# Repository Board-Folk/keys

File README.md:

# Retro Keyboard and Keyboard Adapter Repository

This is repository for retro keyboards and adapters that have been used for projects over the past few years originally intended for private use helping with other projects.

As people have been asking it was thought it'd be worthwhile putting them somewhere in case they're of use to anyone else. Many have just been prototypes and not many have been finished, 
but I'll add them as I go. 'More Fun Making It' Lee showed the finished Acorn Electron PS/2 interface in one of his videos about Mogwaay's Electron ULA replacement work, so I'm starting there.

In complement to the Electron interface, the BBC B/B+ PS/2 and USB and BBC Master PS/2 adapters have been completed, they plug on the keyboard headers too, they need finishing up a bit. BBC B ones now uploaded.

There are many more to add after that too. May add replica keyboard / Cherry MX boards to here also.

Please feel free to make these yourself. Most project folders contain at least their gerbers and code. There's no guarantee anything works. Try help, improve and share if you can.

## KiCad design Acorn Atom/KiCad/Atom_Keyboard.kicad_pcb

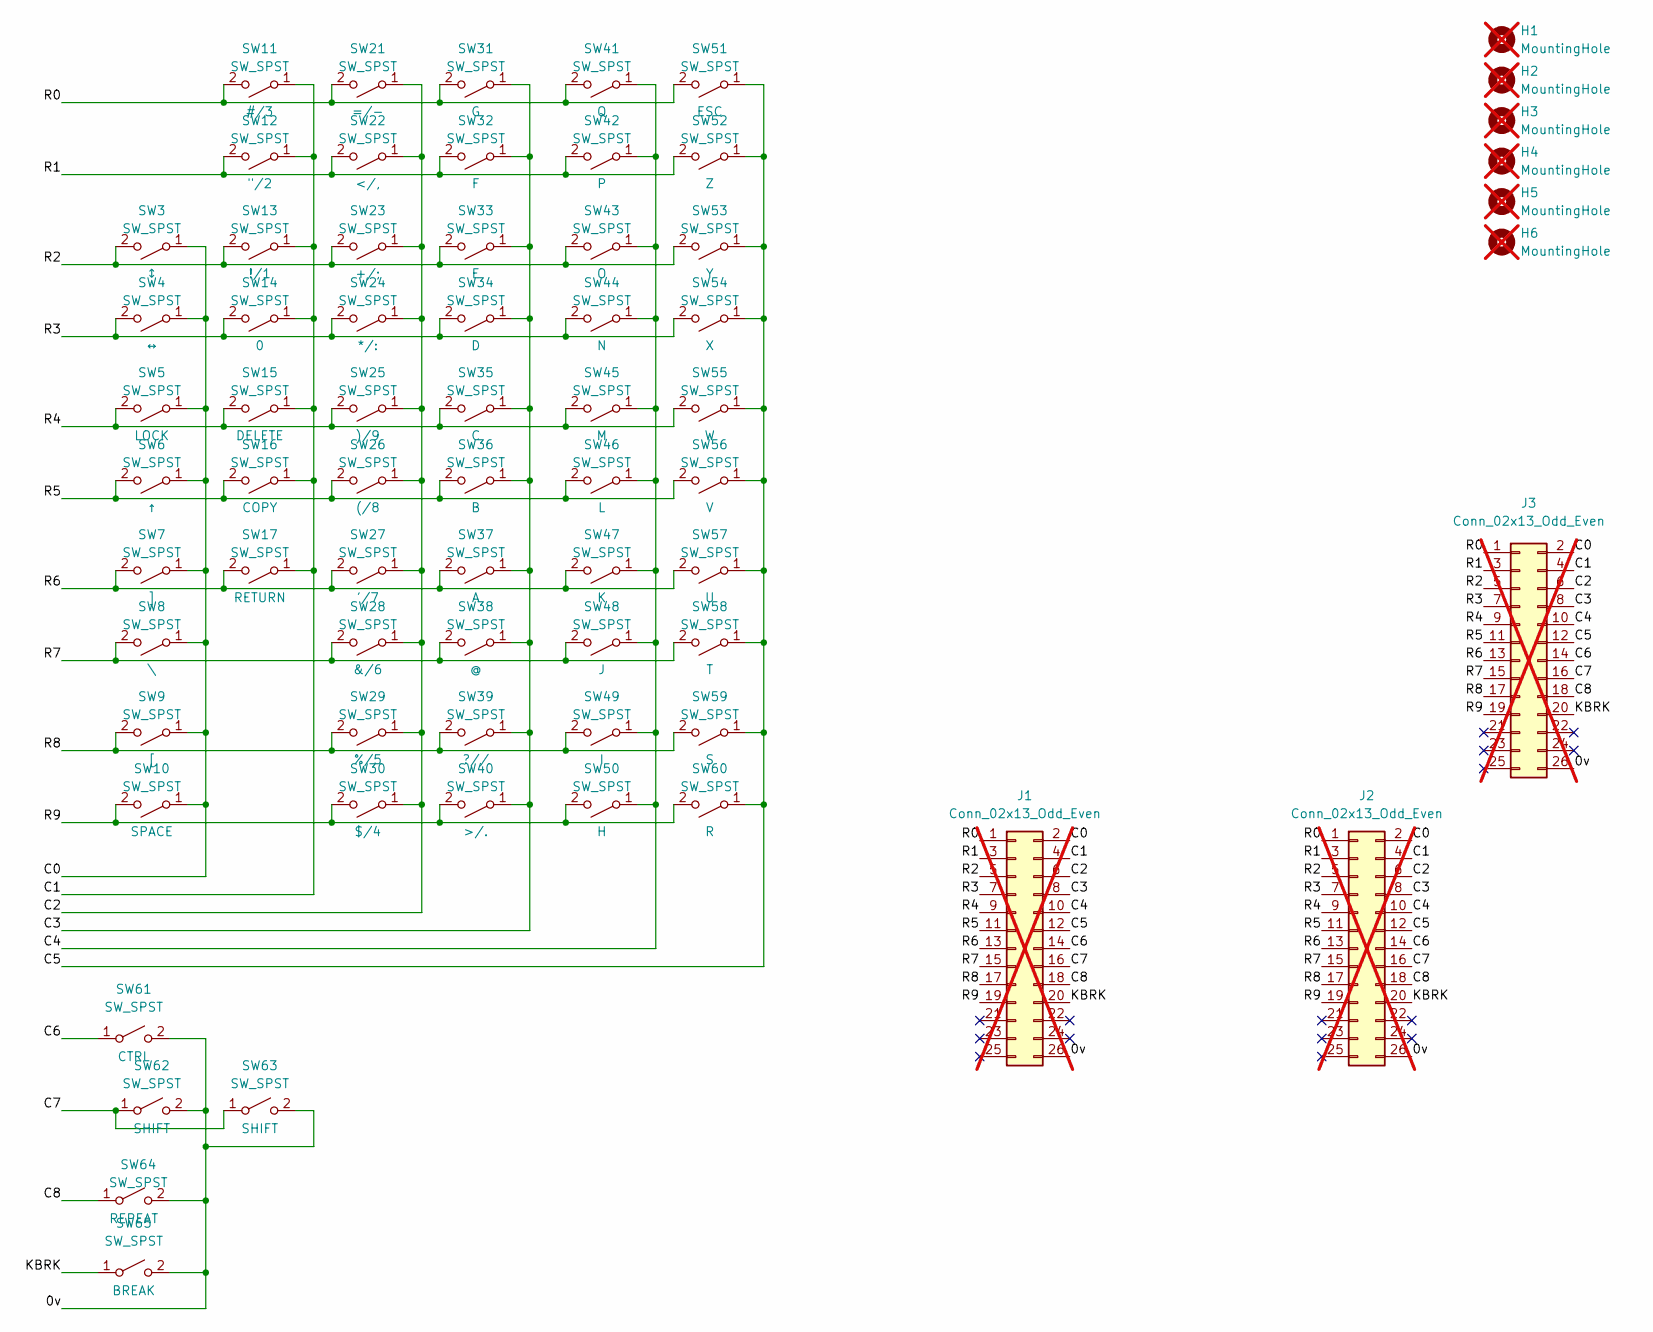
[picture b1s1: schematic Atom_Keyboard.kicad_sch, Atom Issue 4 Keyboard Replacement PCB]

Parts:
H1, H2, H3, H4, H5, H6: MountingHole; MountingHole_2.7mm_M2.5_DIN965; not fitted
J1, J2, J3: Conn_02x13_Odd_Even; IDC-Header_2x13_P2.54mm_Vertical; not fitted
SW3, SW4, SW5, SW6, SW7, SW8, SW9, SW11, SW12, SW13, SW14, SW15, SW16, SW17, SW21, SW22, SW23, SW24, SW25, SW26, SW27, SW28, SW29, SW30, SW31, SW32, SW33, SW34, SW35, SW36, SW37, SW38, SW39, SW40, SW41, SW42, SW43, SW44, SW45, SW46, SW47, SW48, SW49, SW50, SW51, SW52, SW53, SW54, SW55, SW56, SW57, SW58, SW59, SW60, SW61, SW62, SW63, SW64, SW65: SW_SPST; SW_Cherry_MX_1.00u_PCB
SW10: SW_SPST; SW_Cherry_MX_6.25u_PCB

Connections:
/0v: J1.26, J2.26, J3.26, SW61.2 (B), SW62.2 (B), SW63.2 (B), SW64.2 (B), SW65.2 (B)
/C0: J1.2, J2.2, J3.2, SW3.1 (A), SW4.1 (A), SW5.1 (A), SW6.1 (A), SW7.1 (A), SW8.1 (A), SW9.1 (A), SW10.1 (A)
/C1: J1.4, J2.4, J3.4, SW11.1 (A), SW12.1 (A), SW13.1 (A), SW14.1 (A), SW15.1 (A), SW16.1 (A), SW17.1 (A)
/C2: J1.6, J2.6, J3.6, SW21.1 (A), SW22.1 (A), SW23.1 (A), SW24.1 (A), SW25.1 (A), SW26.1 (A), SW27.1 (A), SW28.1 (A), SW29.1 (A), SW30.1 (A)
/C3: J1.8, J2.8, J3.8, SW31.1 (A), SW32.1 (A), SW33.1 (A), SW34.1 (A), SW35.1 (A), SW36.1 (A), SW37.1 (A), SW38.1 (A), SW39.1 (A), SW40.1 (A)
/C4: J1.10, J2.10, J3.10, SW41.1 (A), SW42.1 (A), SW43.1 (A), SW44.1 (A), SW45.1 (A), SW46.1 (A), SW47.1 (A), SW48.1 (A), SW49.1 (A), SW50.1 (A)
/C5: J1.12, J2.12, J3.12, SW51.1 (A), SW52.1 (A), SW53.1 (A), SW54.1 (A), SW55.1 (A), SW56.1 (A), SW57.1 (A), SW58.1 (A), SW59.1 (A), SW60.1 (A)
/C6: J1.14, J2.14, J3.14, SW61.1 (A)
/C7: J1.16, J2.16, J3.16, SW62.1 (A), SW63.1 (A)
/C8: J1.18, J2.18, J3.18, SW64.1 (A)
/KBRK: J1.20, J2.20, J3.20, SW65.1 (A)
/R0: J1.1, J2.1, J3.1, SW11.2 (B), SW21.2 (B), SW31.2 (B), SW41.2 (B), SW51.2 (B)
/R1: J1.3, J2.3, J3.3, SW12.2 (B), SW22.2 (B), SW32.2 (B), SW42.2 (B), SW52.2 (B)
/R2: J1.5, J2.5, J3.5, SW3.2 (B), SW13.2 (B), SW23.2 (B), SW33.2 (B), SW43.2 (B), SW53.2 (B)
/R3: J1.7, J2.7, J3.7, SW4.2 (B), SW14.2 (B), SW24.2 (B), SW34.2 (B), SW44.2 (B), SW54.2 (B)
/R4: J1.9, J2.9, J3.9, SW5.2 (B), SW15.2 (B), SW25.2 (B), SW35.2 (B), SW45.2 (B), SW55.2 (B)
/R5: J1.11, J2.11, J3.11, SW6.2 (B), SW16.2 (B), SW26.2 (B), SW36.2 (B), SW46.2 (B), SW56.2 (B)
/R6: J1.13, J2.13, J3.13, SW7.2 (B), SW17.2 (B), SW27.2 (B), SW37.2 (B), SW47.2 (B), SW57.2 (B)
/R7: J1.15, J2.15, J3.15, SW8.2 (B), SW28.2 (B), SW38.2 (B), SW48.2 (B), SW58.2 (B)
/R8: J1.17, J2.17, J3.17, SW9.2 (B), SW29.2 (B), SW39.2 (B), SW49.2 (B), SW59.2 (B)
/R9: J1.19, J2.19, J3.19, SW10.2 (B), SW30.2 (B), SW40.2 (B), SW50.2 (B), SW60.2 (B)

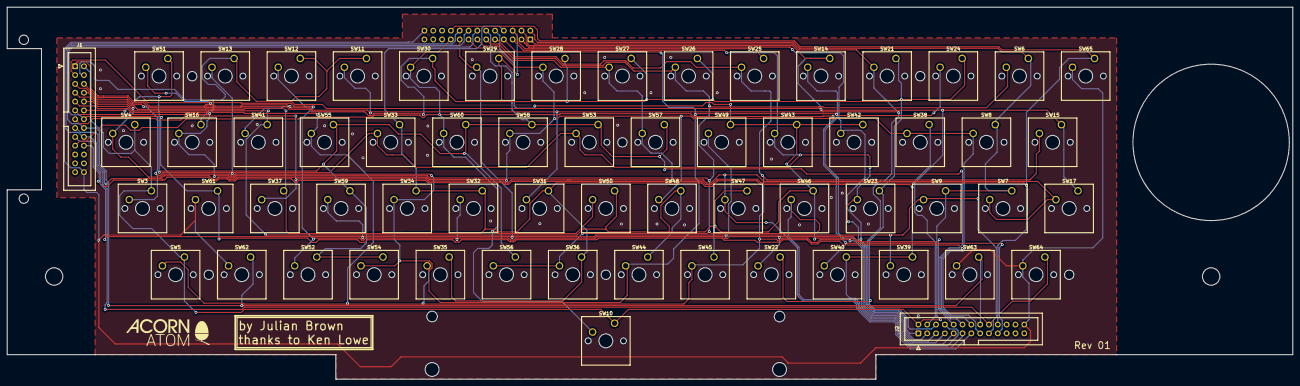
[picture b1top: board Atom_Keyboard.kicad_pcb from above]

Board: 2 copper layers, 370.0 x 107.1 mm, 69 parts (1 on the bottom side), 21 nets.

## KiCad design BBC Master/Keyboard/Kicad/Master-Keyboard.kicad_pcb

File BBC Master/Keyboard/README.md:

# BBC Master 128K (Full Size) Replica Keyboard

A replica keyboard for the full size BBC Master (not Compact). We believe this has been build successfully. Most of the tracks are on the back, former wire links now on the front as tracks.

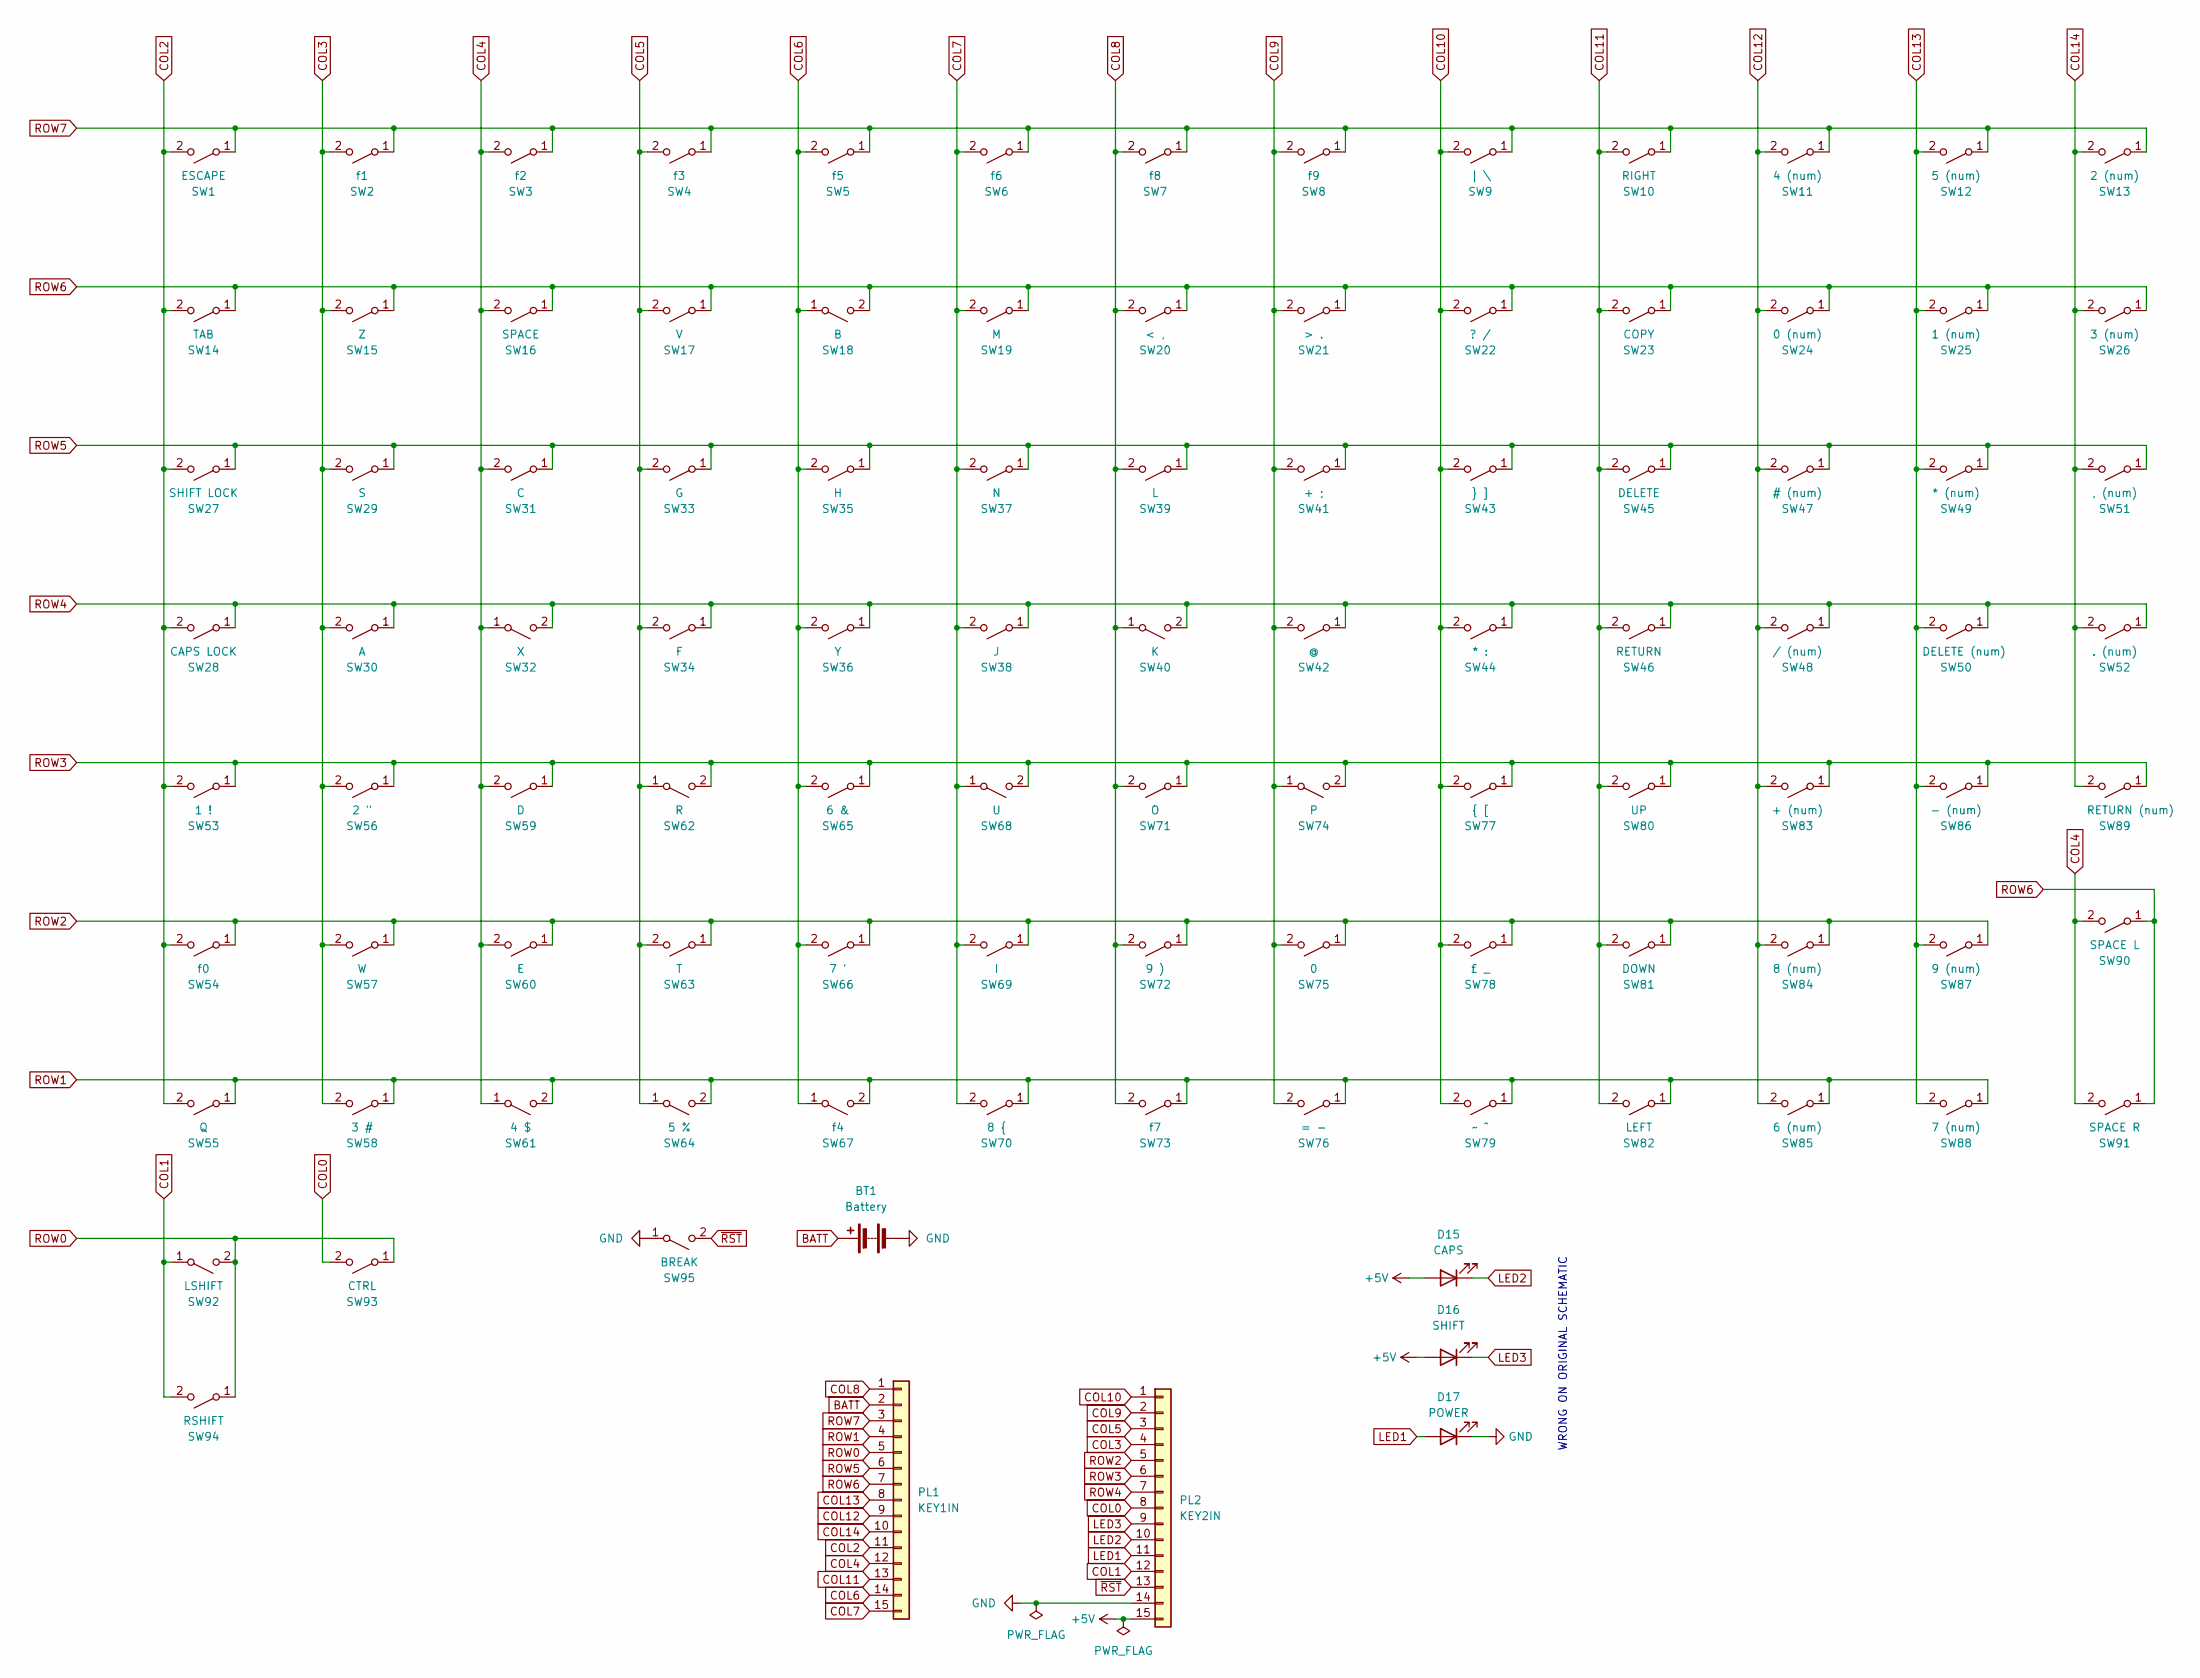
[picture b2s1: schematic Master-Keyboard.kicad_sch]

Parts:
BT1: Battery
D15: CAPS; LED_D2.54mm
D16: SHIFT; LED_D2.54mm
D17: POWER; LED_D2.54mm
PL1: KEY1IN; Header_1x15_P2.54mm
PL2: KEY2IN; Header_1x15_P2.54mm
SW1: ESCAPE; BBC Master KeySwitch
SW2: f1; BBC Master KeySwitch
SW3: f2; BBC Master KeySwitch
SW4: f3; BBC Master KeySwitch
SW5: f5; BBC Master KeySwitch
SW6: f6; BBC Master KeySwitch
SW7: f8; BBC Master KeySwitch
SW8: f9; BBC Master KeySwitch
SW9: | \; BBC Master KeySwitch
SW10: RIGHT; BBC Master KeySwitch
SW11: 4 (num); BBC Master KeySwitch
SW12: 5 (num); BBC Master KeySwitch
SW13: 2 (num); BBC Master KeySwitch
SW14: TAB; BBC Master KeySwitch
SW15: Z; BBC Master KeySwitch
SW16: SPACE; BBC Master KeySwitch
SW17: V; BBC Master KeySwitch
SW18: B; BBC Master KeySwitch
SW19: M; BBC Master KeySwitch
SW20: < ,; BBC Master KeySwitch
SW21: > .; BBC Master KeySwitch
SW22: ? /; BBC Master KeySwitch
SW23: COPY; BBC Master KeySwitch
SW24: 0 (num); BBC Master KeySwitch
SW25: 1 (num); BBC Master KeySwitch
SW26: 3 (num); BBC Master KeySwitch
SW27: SHIFT LOCK; BBC Master KeySwitch
SW28: CAPS LOCK; BBC Master KeySwitch
SW29: S; BBC Master KeySwitch
SW30: A; BBC Master KeySwitch
SW31: C; BBC Master KeySwitch
SW32: X; BBC Master KeySwitch
SW33: G; BBC Master KeySwitch
SW34: F; BBC Master KeySwitch
SW35: H; BBC Master KeySwitch
SW36: Y; BBC Master KeySwitch
SW37: N; BBC Master KeySwitch
SW38: J; BBC Master KeySwitch
SW39: L; BBC Master KeySwitch
SW40: K; BBC Master KeySwitch
SW41: + ;; BBC Master KeySwitch
SW42: @; BBC Master KeySwitch
SW43: } ]; BBC Master KeySwitch
SW44: * :; BBC Master KeySwitch
SW45: DELETE; BBC Master KeySwitch
SW46: RETURN; BBC Master KeySwitch
SW47: # (num); BBC Master KeySwitch
SW48: / (num); BBC Master KeySwitch
SW49: * (num); BBC Master KeySwitch
SW50: DELETE (num); BBC Master KeySwitch
SW51: , (num); BBC Master KeySwitch
SW52: . (num); BBC Master KeySwitch
SW53: 1 !; BBC Master KeySwitch
SW54: f0; BBC Master KeySwitch
SW55: Q; BBC Master KeySwitch
SW56: 2 "; BBC Master KeySwitch
SW57: W; BBC Master KeySwitch
SW58: 3 #; BBC Master KeySwitch
SW59: D; BBC Master KeySwitch
SW60: E; BBC Master KeySwitch
SW61: 4 $; BBC Master KeySwitch
SW62: R; BBC Master KeySwitch
SW63: T; BBC Master KeySwitch
SW64: 5 %; BBC Master KeySwitch
SW65: 6 &; BBC Master KeySwitch
SW66: 7 '; BBC Master KeySwitch
SW67: f4; BBC Master KeySwitch
SW68: U; BBC Master KeySwitch
SW69: I; BBC Master KeySwitch
SW70: 8 {; BBC Master KeySwitch
SW71: O; BBC Master KeySwitch
SW72: 9 ); BBC Master KeySwitch
SW73: f7; BBC Master KeySwitch
SW74: P; BBC Master KeySwitch
SW75: 0; BBC Master KeySwitch
SW76: = -; BBC Master KeySwitch
SW77: { [; BBC Master KeySwitch
SW78: £ _; BBC Master KeySwitch
SW79: ~ ^; BBC Master KeySwitch
SW80: UP; BBC Master KeySwitch
SW81: DOWN; BBC Master KeySwitch
SW82: LEFT; BBC Master KeySwitch
SW83: + (num); BBC Master KeySwitch
SW84: 8 (num); BBC Master KeySwitch
SW85: 6 (num); BBC Master KeySwitch
SW86: - (num); BBC Master KeySwitch
SW87: 9 (num); BBC Master KeySwitch
SW88: 7 (num); BBC Master KeySwitch
SW89: RETURN (num); BBC Master KeySwitch
SW90: SPACE L; BBC Master KeySwitch
SW91: SPACE R; BBC Master KeySwitch
SW92: LSHIFT; BBC Master KeySwitch
SW93: CTRL; BBC Master KeySwitch
SW94: RSHIFT; BBC Master KeySwitch
SW95: BREAK; BBC Master KeySwitch

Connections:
+5V: D15.2 (A), D16.2 (A), PL2.15
BATT: BT1.1 (+), PL1.2
COL0: PL2.8, SW93.2 (B)
COL1: PL2.12, SW92.1 (A), SW94.2 (B)
COL2: PL1.11, SW1.2 (B), SW14.2 (B), SW27.2 (B), SW28.2 (B), SW53.2 (B), SW54.2 (B), SW55.2 (B)
COL3: PL2.4, SW2.2 (B), SW15.2 (B), SW29.2 (B), SW30.2 (B), SW56.2 (B), SW57.2 (B), SW58.2 (B)
COL4: PL1.12, SW3.2 (B), SW16.2 (B), SW31.2 (B), SW32.1 (A), SW59.2 (B), SW60.2 (B), SW61.1 (A), SW90.2 (B), SW91.2 (B)
COL5: PL2.3, SW4.2 (B), SW17.2 (B), SW33.2 (B), SW34.2 (B), SW62.1 (A), SW63.2 (B), SW64.1 (A)
COL6: PL1.14, SW5.2 (B), SW18.1 (A), SW35.2 (B), SW36.2 (B), SW65.2 (B), SW66.2 (B), SW67.1 (A)
COL7: PL1.15, SW6.2 (B), SW19.2 (B), SW37.2 (B), SW38.2 (B), SW68.1 (A), SW69.2 (B), SW70.2 (B)
COL8: PL1.1, SW7.2 (B), SW20.2 (B), SW39.2 (B), SW40.1 (A), SW71.2 (B), SW72.2 (B), SW73.2 (B)
COL9: PL2.2, SW8.2 (B), SW21.2 (B), SW41.2 (B), SW42.2 (B), SW74.1 (A), SW75.2 (B), SW76.2 (B)
COL10: PL2.1, SW9.2 (B), SW22.2 (B), SW43.2 (B), SW44.2 (B), SW77.2 (B), SW78.2 (B), SW79.2 (B)
COL11: PL1.13, SW10.2 (B), SW23.2 (B), SW45.2 (B), SW46.2 (B), SW80.2 (B), SW81.2 (B), SW82.2 (B)
COL12: PL1.9, SW11.2 (B), SW24.2 (B), SW47.2 (B), SW48.2 (B), SW83.2 (B), SW84.2 (B), SW85.2 (B)
COL13: PL1.8, SW12.2 (B), SW25.2 (B), SW49.2 (B), SW50.2 (B), SW86.2 (B), SW87.2 (B), SW88.2 (B)
COL14: PL1.10, SW13.2 (B), SW26.2 (B), SW51.2 (B), SW52.2 (B), SW89.2 (B)
GND: BT1.2 (-), D17.1 (K), PL2.14, SW95.1 (A)
LED1: D17.2 (A), PL2.11
LED2: D15.1 (K), PL2.10
LED3: D16.1 (K), PL2.9
ROW0: PL1.5, SW92.2 (B), SW93.1 (A), SW94.1 (A)
ROW1: PL1.4, SW55.1 (A), SW58.1 (A), SW61.2 (B), SW64.2 (B), SW67.2 (B), SW70.1 (A), SW73.1 (A), SW76.1 (A), SW79.1 (A), SW82.1 (A), SW85.1 (A), SW88.1 (A)
ROW2: PL2.5, SW54.1 (A), SW57.1 (A), SW60.1 (A), SW63.1 (A), SW66.1 (A), SW69.1 (A), SW72.1 (A), SW75.1 (A), SW78.1 (A), SW81.1 (A), SW84.1 (A), SW87.1 (A)
ROW3: PL2.6, SW53.1 (A), SW56.1 (A), SW59.1 (A), SW62.2 (B), SW65.1 (A), SW68.2 (B), SW71.1 (A), SW74.2 (B), SW77.1 (A), SW80.1 (A), SW83.1 (A), SW86.1 (A), SW89.1 (A)
ROW4: PL2.7, SW28.1 (A), SW30.1 (A), SW32.2 (B), SW34.1 (A), SW36.1 (A), SW38.1 (A), SW40.2 (B), SW42.1 (A), SW44.1 (A), SW46.1 (A), SW48.1 (A), SW50.1 (A), SW52.1 (A)
ROW5: PL1.6, SW27.1 (A), SW29.1 (A), SW31.1 (A), SW33.1 (A), SW35.1 (A), SW37.1 (A), SW39.1 (A), SW41.1 (A), SW43.1 (A), SW45.1 (A), SW47.1 (A), SW49.1 (A), SW51.1 (A)
ROW6: PL1.7, SW14.1 (A), SW15.1 (A), SW16.1 (A), SW17.1 (A), SW18.2 (B), SW19.1 (A), SW20.1 (A), SW21.1 (A), SW22.1 (A), SW23.1 (A), SW24.1 (A), SW25.1 (A), SW26.1 (A), SW90.1 (A), SW91.1 (A)
ROW7: PL1.3, SW1.1 (A), SW2.1 (A), SW3.1 (A), SW4.1 (A), SW5.1 (A), SW6.1 (A), SW7.1 (A), SW8.1 (A), SW9.1 (A), SW10.1 (A), SW11.1 (A), SW12.1 (A), SW13.1 (A)
~RST: PL2.13, SW95.2 (B)

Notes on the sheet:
WRONG ON ORIGINAL SCHEMATIC

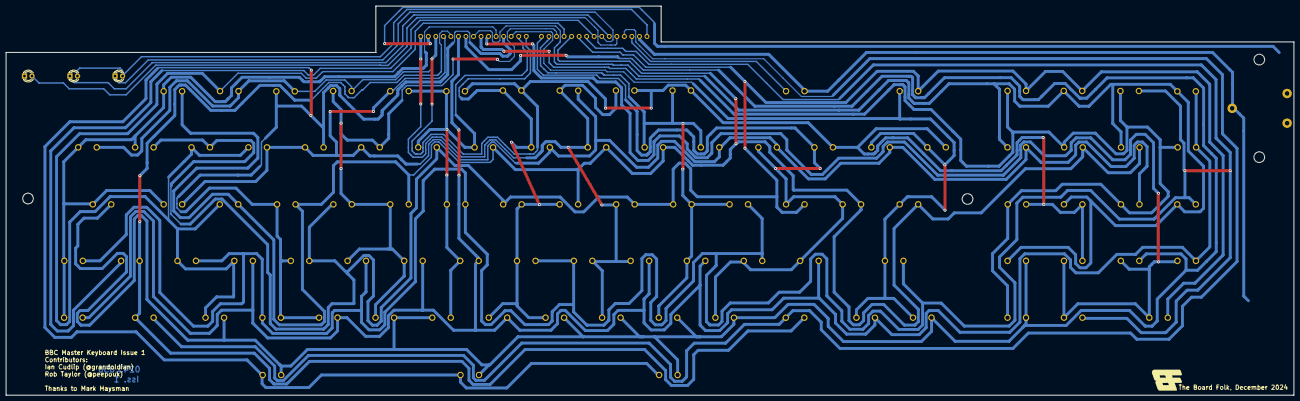
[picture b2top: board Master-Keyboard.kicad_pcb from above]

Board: 2 copper layers, 434.0 x 131.1 mm, 101 parts (0 on the bottom side), 30 nets.

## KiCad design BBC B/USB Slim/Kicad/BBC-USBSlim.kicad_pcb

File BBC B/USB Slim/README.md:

# BBC B/B+ USB Slim v1

This is a surface mount board designed to fit inside the BBC's case, though currently does not work with the original keyboard connected. Uses the Seeduino XIAO. The XIAO does take a few seconds to boot and recognise the keyboard, it's not as quick as the Atmega version.

* BOM

iBOM for the board.

* Gerber

Gerbers and gerber zip file for production.

* Kicad

Kicad project for the board.

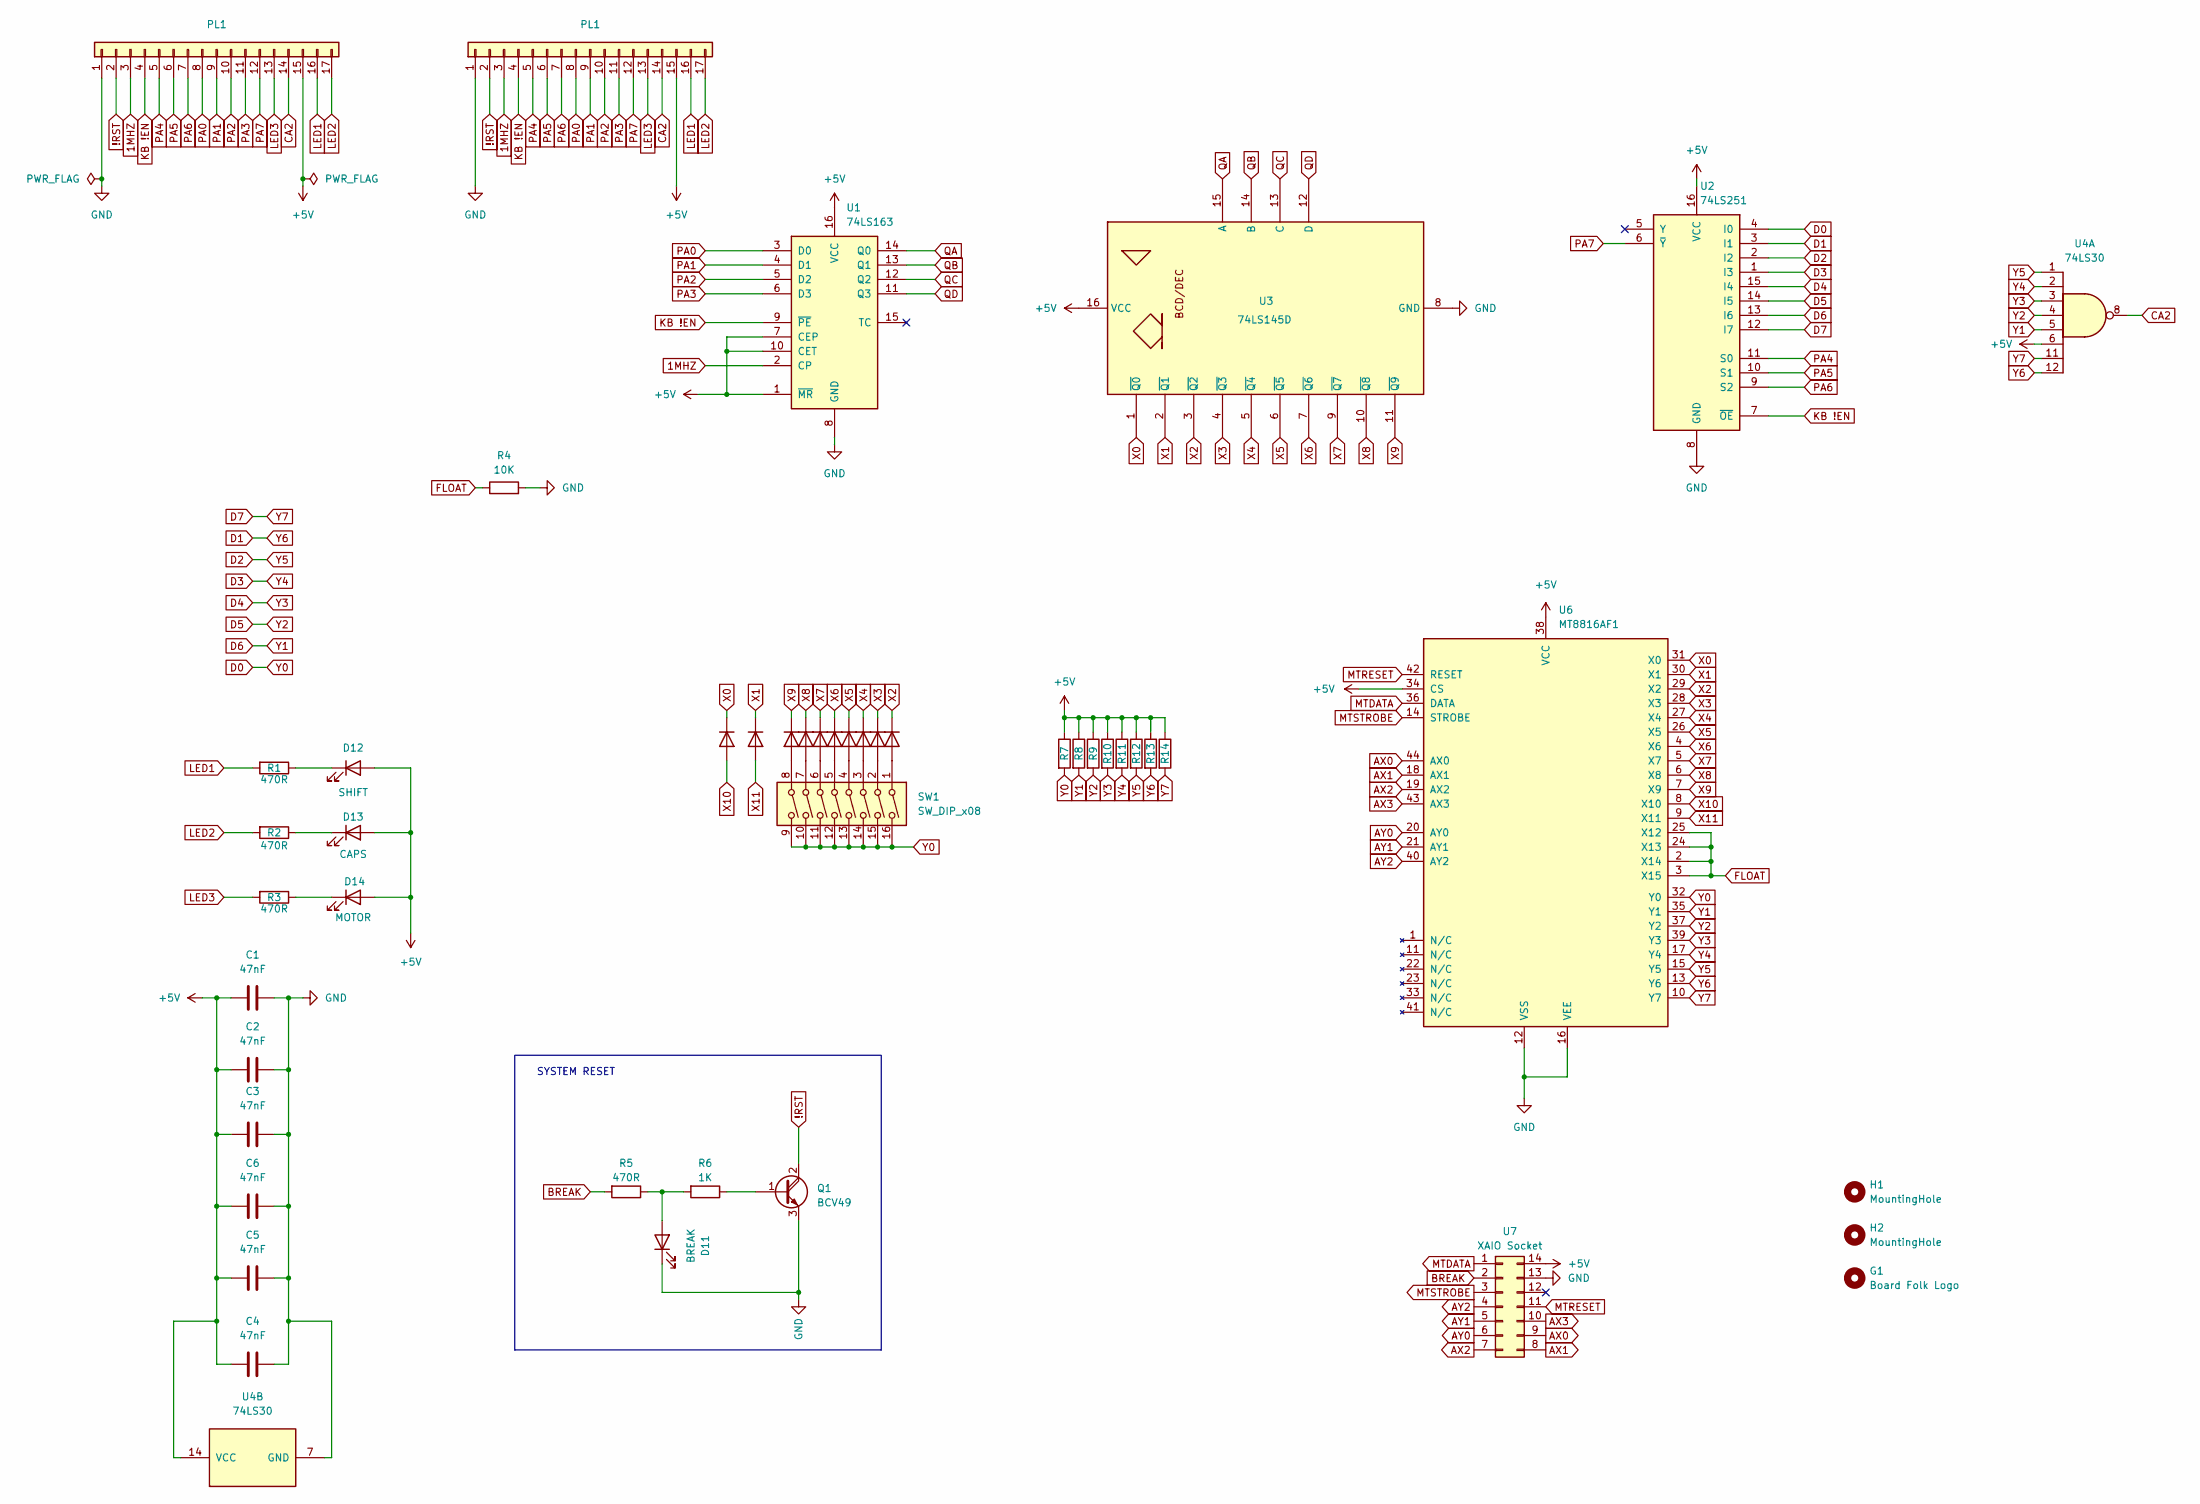
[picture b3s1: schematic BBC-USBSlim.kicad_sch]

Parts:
C1, C2, C3, C4, C5, C6: 47nF; C_0805_2012Metric
D1, D2, D3, D4, D5, D6, D7, D8, D9, D10: 1N4148; MINIDIODE
D11: BREAK; LED_1206_3216Metric
D12: SHIFT; LED_1206_3216Metric
D13: CAPS; LED_1206_3216Metric
D14: MOTOR; LED_1206_3216Metric
G1: Board Folk Logo; BF8
H1, H2: MountingHole; MountingHole_2.5mm
J1, J3: PL1; PinHeader_1x17_P2.54mm_Vertical
Q1: BCV49; SOT-89-3
R1, R2, R3, R5: 470R; R_0805_2012Metric
R4: 10K; R_0805_2012Metric
R6: 1K; R_0805_2012Metric
R7, R8, R9, R10, R11, R12, R13, R14: 2K2; R_0805_2012Metric
SW1: SW_DIP_x08; DIP-16_W7.62mm
U1: 74LS163; SOIC-16_3.9x9.9mm_P1.27mm
U2: 74LS251; SOIC-16_3.9x9.9mm_P1.27mm
U3: 74LS145D; SOIC-16_3.9x9.9mm_P1.27mm
U4: 74LS30; SOIC-14_3.9x8.7mm_P1.27mm
U6: MT8816AF1; TQFP-44_10x10mm_P0.8mm
U7: XAIO Socket; XAIO 14PIN

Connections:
1MHZ: J1.3, J3.3, U1.2 (CP)
!RST: J1.2, J3.2, Q1.2 (C)
+5V: C1.1, C2.1, C3.1, C4.1, C5.1, C6.1, D12.2 (A), D13.2 (A), D14.2 (A), J1.15, J3.15, R7.1, R8.1, R9.1, R10.1, R11.1, R12.1, R13.1, R14.1, U1.1 (~MR), U1.7 (CEP), U1.10 (CET), U1.16 (VCC), U2.16 (VCC), U3.16 (VCC), U4.6, U4.14 (VCC), U6.34 (CS), U6.38 (VCC), U7.14
AX0: U6.44 (AX0), U7.9
AX1: U6.18 (AX1), U7.8
AX2: U6.19 (AX2), U7.7
AX3: U6.43 (AX3), U7.10
AY0: U6.20 (AY0), U7.6
AY1: U6.21 (AY1), U7.5
AY2: U6.40 (AY2), U7.4
BREAK: R5.2, U7.2
CA2: J1.14, J3.14, U4.8
D0: R7.2, SW1.9, SW1.10, SW1.11, SW1.12, SW1.13, SW1.14, SW1.15, SW1.16, U2.4 (I0), U6.32 (Y0)
D1: R13.2, U2.3 (I1), U4.12, U6.13 (Y6)
D2: R12.2, U2.2 (I2), U4.1, U6.15 (Y5)
D3: R11.2, U2.1 (I3), U4.2, U6.17 (Y4)
D4: R10.2, U2.15 (I4), U4.3, U6.39 (Y3)
D5: R9.2, U2.14 (I5), U4.4, U6.37 (Y2)
D6: R8.2, U2.13 (I6), U4.5, U6.35 (Y1)
D7: R14.2, U2.12 (I7), U4.11, U6.10 (Y7)
FLOAT: R4.1, U6.2 (X14), U6.3 (X15), U6.24 (X13), U6.25 (X12)
GND: C1.2, C2.2, C3.2, C4.2, C5.2, C6.2, D11.1 (K), J1.1, J3.1, Q1.3 (E), R4.2, U1.8 (GND), U2.8 (GND), U3.8 (GND), U4.7 (GND), U6.12 (VSS), U6.16 (VEE), U7.13
KB !EN: J1.4, J3.4, U1.9 (~PE), U2.7 (~OE)
LED1: J1.16, J3.16, R1.2
LED2: J1.17, J3.17, R2.2
LED3: J1.13, J3.13, R3.2
MTDATA: U6.36 (DATA), U7.1
MTRESET: U6.42 (RESET), U7.11
MTSTROBE: U6.14 (STROBE), U7.3
unnamed: D3.2 (A), SW1.1
unnamed: D4.2 (A), SW1.2
unnamed: D5.2 (A), SW1.3
unnamed: D6.2 (A), SW1.4
unnamed: D7.2 (A), SW1.5
unnamed: D8.2 (A), SW1.6
unnamed: D9.2 (A), SW1.7
unnamed: D10.2 (A), SW1.8
unnamed: D11.2 (A), R5.1, R6.2
unnamed: D12.1 (K), R1.1
unnamed: D13.1 (K), R2.1
unnamed: D14.1 (K), R3.1
unnamed: Q1.1 (B), R6.1
PA0: J1.8, J3.8, U1.3 (D0)
PA1: J1.9, J3.9, U1.4 (D1)
PA2: J1.10, J3.10, U1.5 (D2)
PA3: J1.11, J3.11, U1.6 (D3)
PA4: J1.5, J3.5, U2.11 (S0)
PA5: J1.6, J3.6, U2.10 (S1)
PA6: J1.7, J3.7, U2.9 (S2)
PA7: J1.12, J3.12, U2.6 (~Y)
QA: U1.14 (Q0), U3.15 (A)
QB: U1.13 (Q1), U3.14 (B)
QC: U1.12 (Q2), U3.13 (C)
QD: U1.11 (Q3), U3.12 (D)
X0: D1.1 (K), U3.1 (~Q0), U6.31 (X0)
X1: D2.1 (K), U3.2 (~Q1), U6.30 (X1)
X2: D3.1 (K), U3.3 (~Q2), U6.29 (X2)
X3: D4.1 (K), U3.4 (~Q3), U6.28 (X3)
X4: D5.1 (K), U3.5 (~Q4), U6.27 (X4)
X5: D6.1 (K), U3.6 (~Q5), U6.26 (X5)
X6: D7.1 (K), U3.7 (~Q6), U6.4 (X6)
X7: D8.1 (K), U3.9 (~Q7), U6.5 (X7)
X8: D9.1 (K), U3.10 (~Q8), U6.6 (X8)
X9: D10.1 (K), U3.11 (~Q9), U6.7 (X9)
X10: D1.2 (A), U6.8 (X10)
X11: D2.2 (A), U6.9 (X11)

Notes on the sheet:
SYSTEM RESET

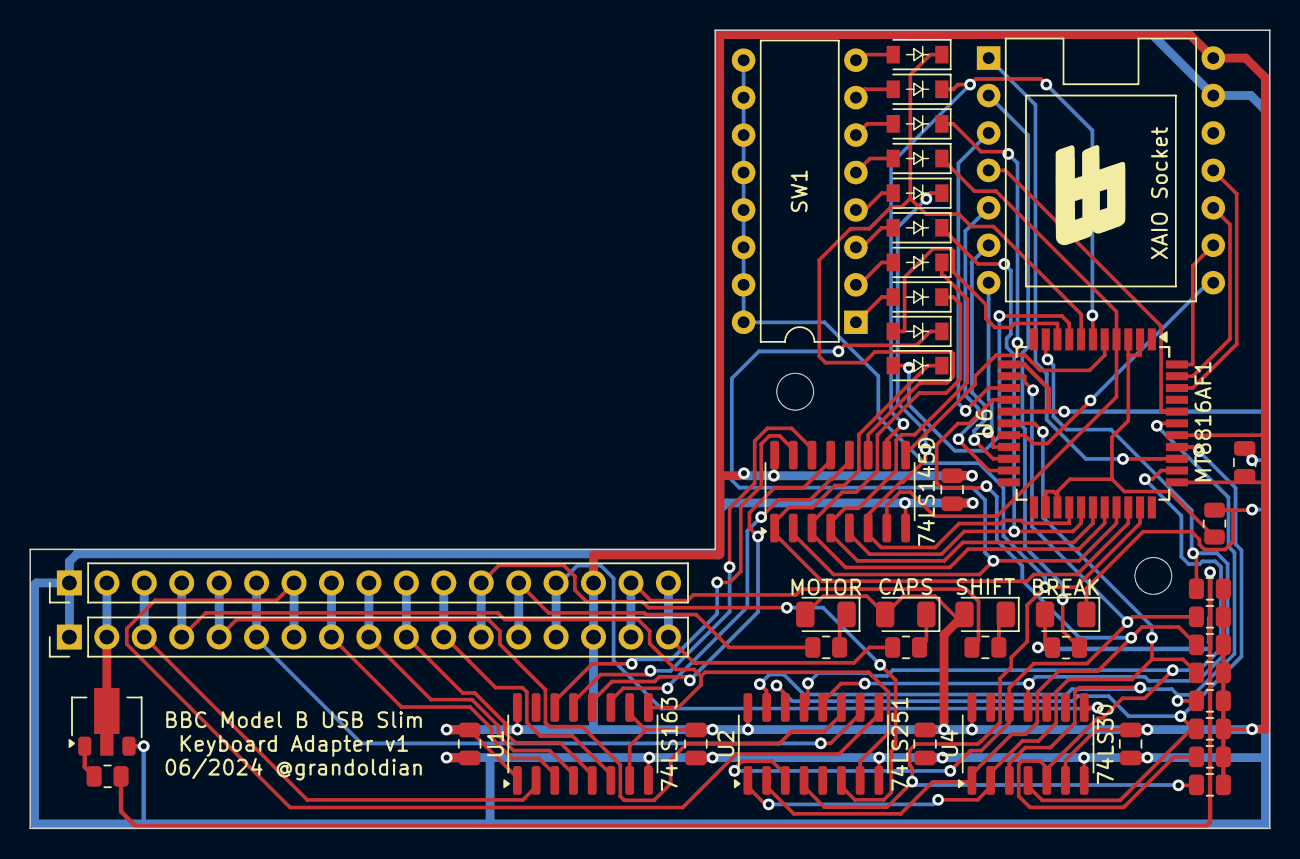
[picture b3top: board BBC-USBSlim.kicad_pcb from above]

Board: 2 copper layers, 84.1 x 54.1 mm, 47 parts (0 on the bottom side), 66 nets.

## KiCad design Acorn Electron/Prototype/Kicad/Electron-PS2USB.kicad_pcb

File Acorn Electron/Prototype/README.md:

# Acorn Electron Prototype Board v0

A PS/2 and potentially USB keyboard interface for the Acorn Electron based on C64keyboard by Robert VanHazinga using an Arduino type board and an MT8816 switch chip. This is the original throughhole board. 
It won't fit inside the case with the lid on, but is easy to build. The PS/2 configuration is for Arduino Nano, the USB, Seeeduino XIAO, same as the original project. USB code not done yet.
You may need to toggle Arduino IDE between processor ATmega328P and ATmega328P (old bootloader) depending on which Nano you have.

* BOM

iBOM for the board.

* Gerber

Gerbers and gerber zip file for production.

* Kicad

Kicad project for the board.

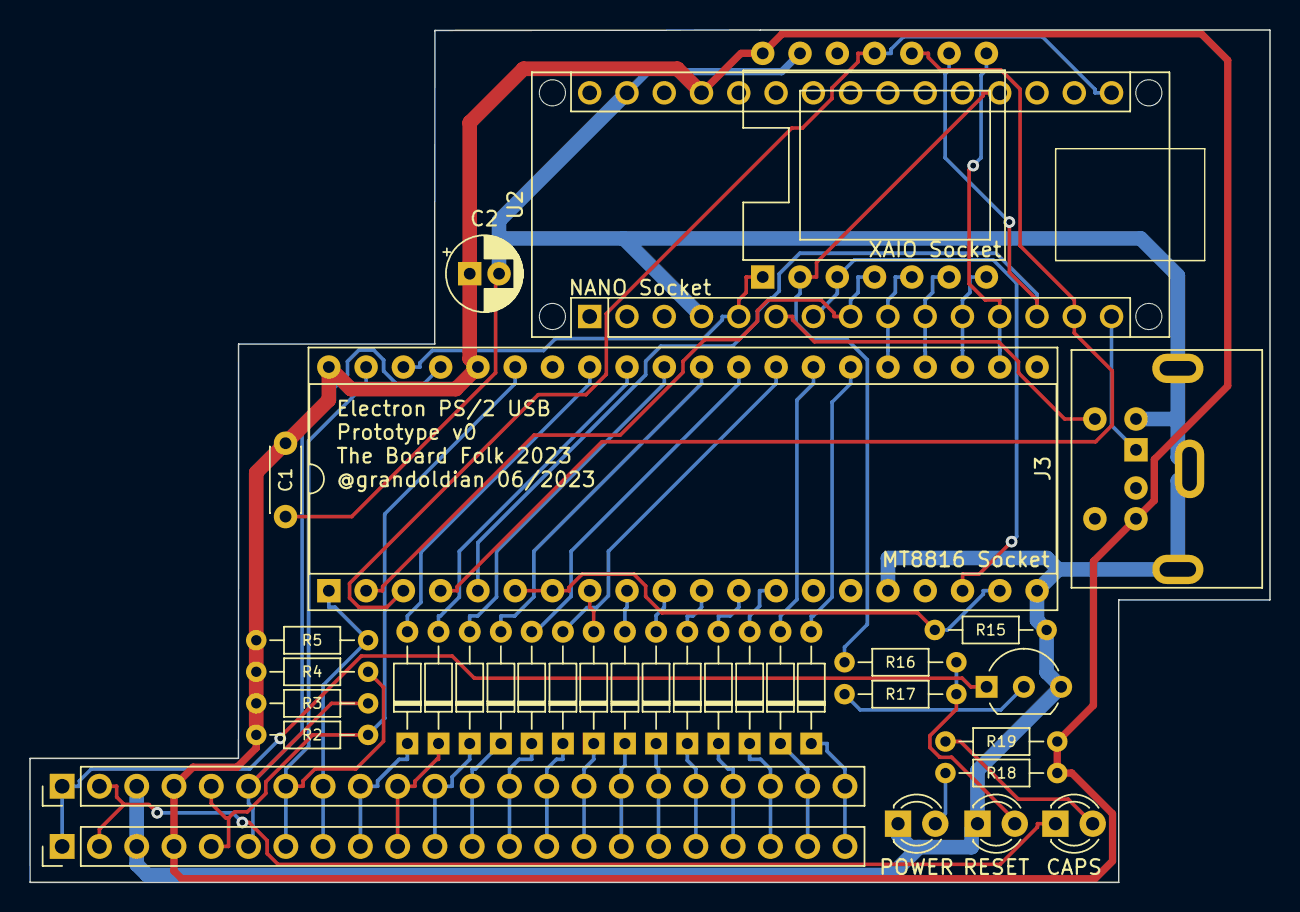
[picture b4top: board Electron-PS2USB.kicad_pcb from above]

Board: 2 copper layers, 84.5 x 58.1 mm, 35 parts (0 on the bottom side), 54 nets.

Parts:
C1: 47nF; C_Disc_D4.3mm_W1.9mm_P5.00mm
C2: 47uF; CP_Radial_D5.0mm_P2.00mm
CP1, CP2: KEYBOARD; PinHeader_1x22_P2.54mm_Vertical
D1, D2, D3, D4, D5, D6, D7, D8, D9, D10, D11, D12, D13, D14: D; D_DO-34_SOD68_P7.62mm_Horizontal
D15: POWER; LED_D3.0mm
D16: RESET; LED_D3.0mm
D17: CAPS; LED_D3.0mm
J3: PS/2; Connector_Mini-DIN_Female_6Pin_2rows
Q1: BC517; TO-92_Inline_Wide
R2, R3, R4, R5: R; R_Axial_DIN0204_L3.6mm_D1.6mm_P7.62mm_Horizontal
R15: 10K; R_Axial_DIN0204_L3.6mm_D1.6mm_P7.62mm_Horizontal
R16: 470R; R_Axial_DIN0204_L3.6mm_D1.6mm_P7.62mm_Horizontal
R17, R18, R19: 1K; R_Axial_DIN0204_L3.6mm_D1.6mm_P7.62mm_Horizontal
U1: MT8816 Socket; DIP-40_W15.24mm_Socket
U2: NANO Socket; Arduino_Nano_WithMountingHoles
U7: XAIO Socket; XAIO 14PIN

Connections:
!RST: CP1.1, CP2.1, Q1.1 (C)
+5V: C1.2, C2.1, CP1.4, CP2.4, J3.4, R2.2, R3.2, R4.2, R5.2, R18.1, R19.1, U1.36, U1.40, U2.27, U7.14
/A0: CP1.18, CP2.18, D10.1 (K)
/A1: CP1.19, CP2.19, D11.1 (K)
/A2: CP1.20, CP2.20, D12.1 (K)
/A3: CP1.21, CP2.21, D13.1 (K)
/A4: CP1.22, CP2.22, D14.1 (K)
/A5: CP1.17, CP2.17, D9.1 (K)
/A6: CP1.16, CP2.16, D8.1 (K)
/A7: CP1.15, CP2.15, D7.1 (K)
/A8: CP1.14, CP2.14, D6.1 (K)
/A9: CP1.13, CP2.13, D5.1 (K)
/A10: CP1.12, CP2.12, D4.1 (K)
/A11: CP1.11, CP2.11, D3.1 (K)
/A12: CP1.10, CP2.10, D2.1 (K)
/A13: CP1.9, CP2.9, D1.1 (K)
AX0: U1.5, U2.13, U7.9
AX1: U1.22, U2.12, U7.8
AX2: U1.23, U2.11, U7.7
AX3: U1.4, U2.14, U7.10
AY0: U1.24, U2.10, U7.6
AY1: U1.25, U2.9, U7.5
AY2: U1.2, U2.8, U7.4
BREAK: R16.2, U2.19, U7.2
CAPSLOCK: CP1.2, CP2.2, D17.1 (K)
COL0: D1.2 (A), U1.33
COL1: D2.2 (A), U1.32
COL2: D3.2 (A), U1.31
COL3: D4.2 (A), U1.30
COL4: D5.2 (A), U1.29
COL5: D6.2 (A), U1.28
COL6: D7.2 (A), U1.8
COL7: D8.2 (A), U1.9
COL8: D9.2 (A), U1.10
COL9: D10.2 (A), U1.11
COL10: D11.2 (A), U1.12
COL11: D12.2 (A), U1.13
COL12: D13.2 (A), U1.27
COL13: D14.2 (A), U1.26
DATA: U1.38, U2.5, U7.1
FLOAT: R15.1, U1.6, U1.7, U1.19
GND: C1.1, C2.2, CP1.3, CP2.3, D15.1 (K), D16.1 (K), J3.3, J3.7, Q1.3 (E), R15.2, U1.16, U1.20, U2.4, U2.29, U7.13
unnamed: D15.2 (A), R18.2
unnamed: D16.2 (A), R16.1, R17.2
unnamed: D17.2 (A), R19.2
unnamed: Q1.2 (B), R17.1
PS2-CLK: J3.5, U2.6
PS2-DATA: J3.1, U2.15
RESET: U1.3, U2.16, U7.11
ROW0: CP1.5, CP2.5, R2.1, U1.35
ROW1: CP1.6, CP2.6, R3.1, U1.37
ROW2: CP1.7, CP2.7, R4.1, U1.39
ROW3: CP1.8, CP2.8, R5.1, U1.1
STROBE: U1.18, U2.7, U7.3
